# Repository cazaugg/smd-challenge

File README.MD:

# Readme of SMD-Challenge PCB

## Project description

This is a little SMD soldering challenge with Moser Baer branding. Used to teach soldering and teach people about electronics.

Version one used 1206 to 0201 chips and is quite difficult. Version two is simplified and only uses 1206 to 0603 cips.

## Workflow and project organization

- [PCB design and part libraries](pcb/pcb-info.md)
- [Documentation](doc/doc-info.md)
- [Production](prod/prod-info.md)

## Tools

Made with KiCad 7.

***(c)2023 by C. Zaugg***

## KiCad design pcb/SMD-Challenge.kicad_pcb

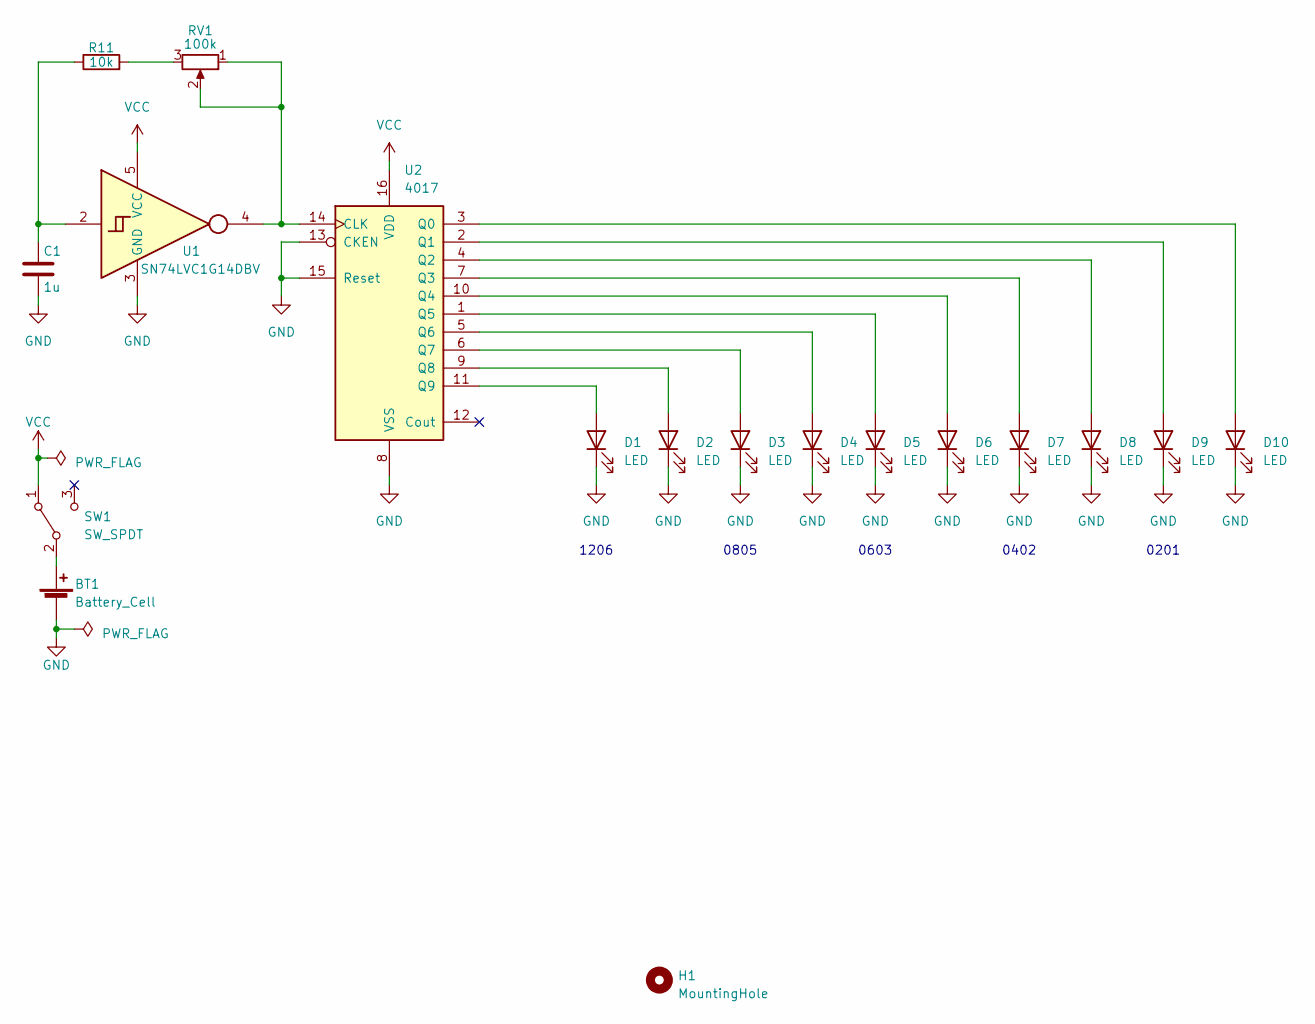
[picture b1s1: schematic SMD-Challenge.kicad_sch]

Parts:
BT1: Battery_Cell; BatteryHolder_Keystone_3002_1x2032
C1: 1u; C_1206_3216Metric
D1, D2: LED; LED_1206_3216Metric
D3, D4: LED; LED_0805_2012Metric
D5, D6: LED; LED_0603_1608Metric
D7, D8: LED; LED_0402_1005Metric
D9, D10: LED; LED_0201_0603Metric
H1: MountingHole; MountingHole_2.2mm_M2
R11: 10k; R_1206_3216Metric
RV1: 100k; Potentiometer_Bourns_TC33X_Vertical
SW1: SW_SPDT; SW_SPDT_PCM12
U1: SN74LVC1G14DBV; SOT-23-5
U2: 4017; SO-16_3.9x9.9mm_P1.27mm

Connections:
GND: BT1.2 (-), C1.2, D1.1 (K), D2.1 (K), D3.1 (K), D4.1 (K), D5.1 (K), D6.1 (K), D7.1 (K), D8.1 (K), D9.1 (K), D10.1 (K), U1.3 (GND), U2.8 (VSS), U2.13 (CKEN), U2.15 (Reset)
unnamed: BT1.1 (+), SW1.2 (B)
unnamed: C1.1, R11.1, U1.2
unnamed: D1.2 (A), U2.11 (Q9)
unnamed: D2.2 (A), U2.9 (Q8)
unnamed: D3.2 (A), U2.6 (Q7)
unnamed: D4.2 (A), U2.5 (Q6)
unnamed: D5.2 (A), U2.1 (Q5)
unnamed: D6.2 (A), U2.10 (Q4)
unnamed: D7.2 (A), U2.7 (Q3)
unnamed: D8.2 (A), U2.4 (Q2)
unnamed: D9.2 (A), U2.2 (Q1)
unnamed: D10.2 (A), U2.3 (Q0)
unnamed: R11.2, RV1.3
unnamed: RV1.1, RV1.2, U1.4, U2.14 (CLK)
VCC: SW1.1 (A), U1.5 (VCC), U2.16 (VDD)

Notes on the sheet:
0201
1206
0805
0402
0603

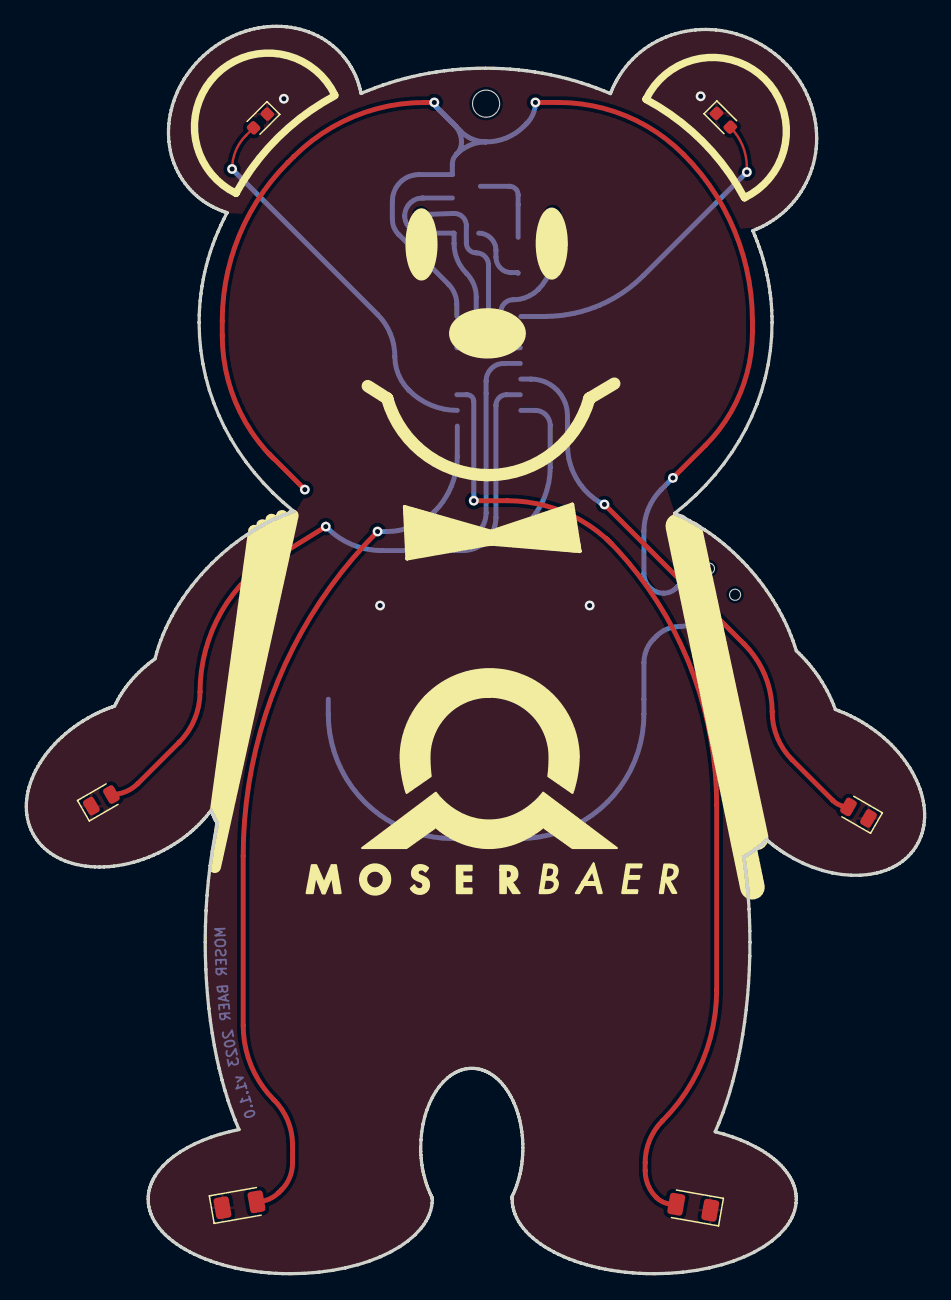
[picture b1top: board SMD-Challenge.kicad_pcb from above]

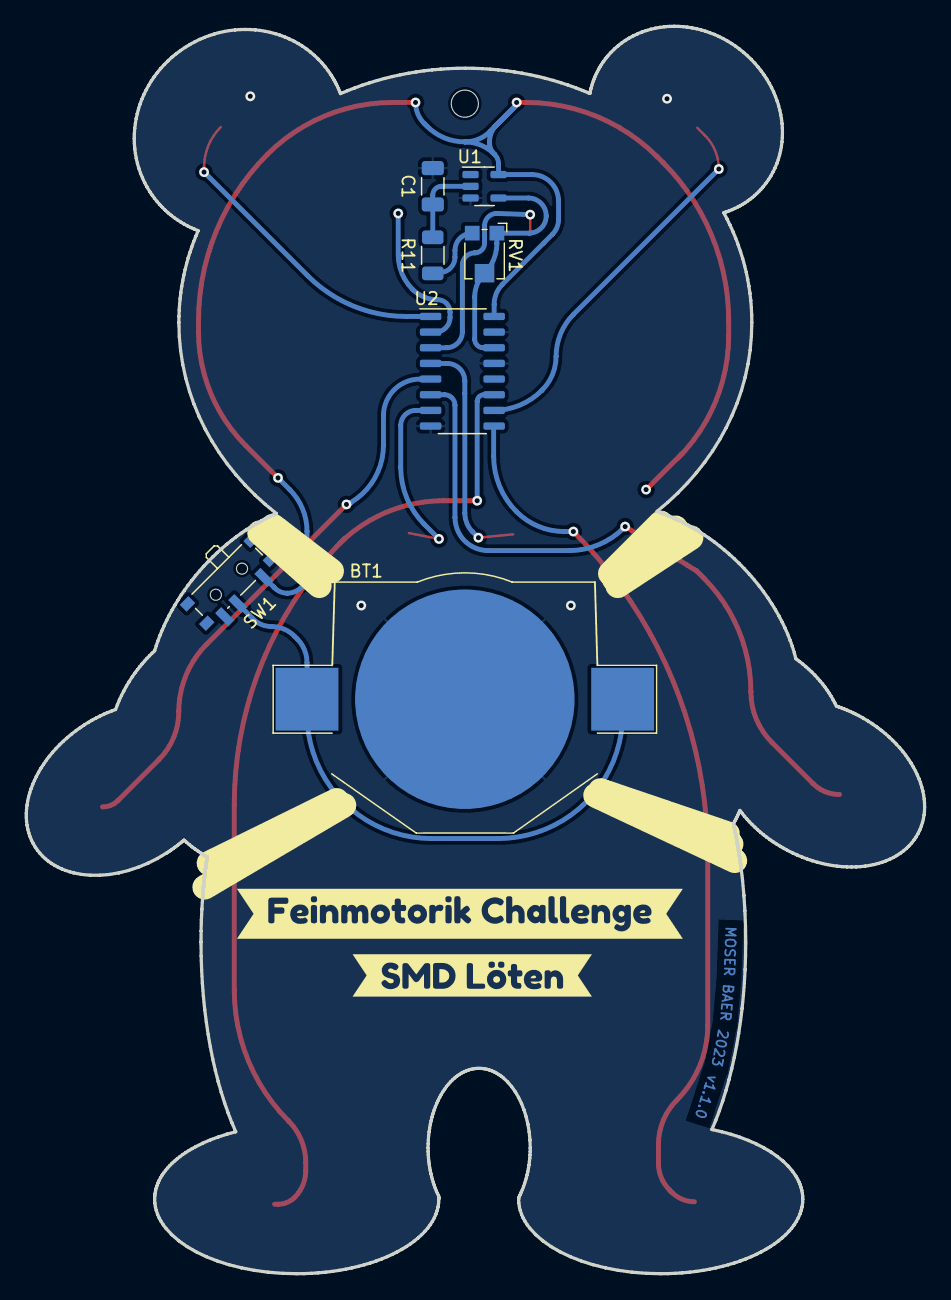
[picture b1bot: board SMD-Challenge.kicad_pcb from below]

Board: 2 copper layers, 72.9 x 101.2 mm, 20 parts (9 on the bottom side), 16 nets.

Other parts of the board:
kibuzzard-63D590DE: G***; kibuzzard-63D590DE
kibuzzard-63D590F7: G***; kibuzzard-63D590F7

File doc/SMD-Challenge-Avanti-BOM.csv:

"#","Reference","Qty","Value","Footprint","DNP"
"1","BT1","1","Battery_Cell","Battery:BatteryHolder_Keystone_3002_1x2032",""
"2","C1","1","1u","Capacitor_SMD:C_1206_3216Metric",""
"3","D1, D2","2","LED","LED_SMD:LED_0603_1608Metric",""
"4","D3, D6","2","LED","LED_SMD:LED_0805_2012Metric",""
"5","D4, D5","2","LED","LED_SMD:LED_1206_3216Metric",""
"6","H1","1","MountingHole","MountingHole:MountingHole_2.5mm",""
"7","R11","1","10k","Resistor_SMD:R_1206_3216Metric",""
"8","RV1","1","100k","Potentiometer_SMD:Potentiometer_Bourns_TC33X_Vertical",""
"9","SW1","1","SW_SPDT","Button_Switch_SMD:SW_SPDT_PCM12",""
"10","U1","1","SN74LVC1G14DBV","Package_TO_SOT_SMD:SOT-23-5",""
"11","U2","1","74HC4017","Package_SO:SO-16_3.9x9.9mm_P1.27mm",""

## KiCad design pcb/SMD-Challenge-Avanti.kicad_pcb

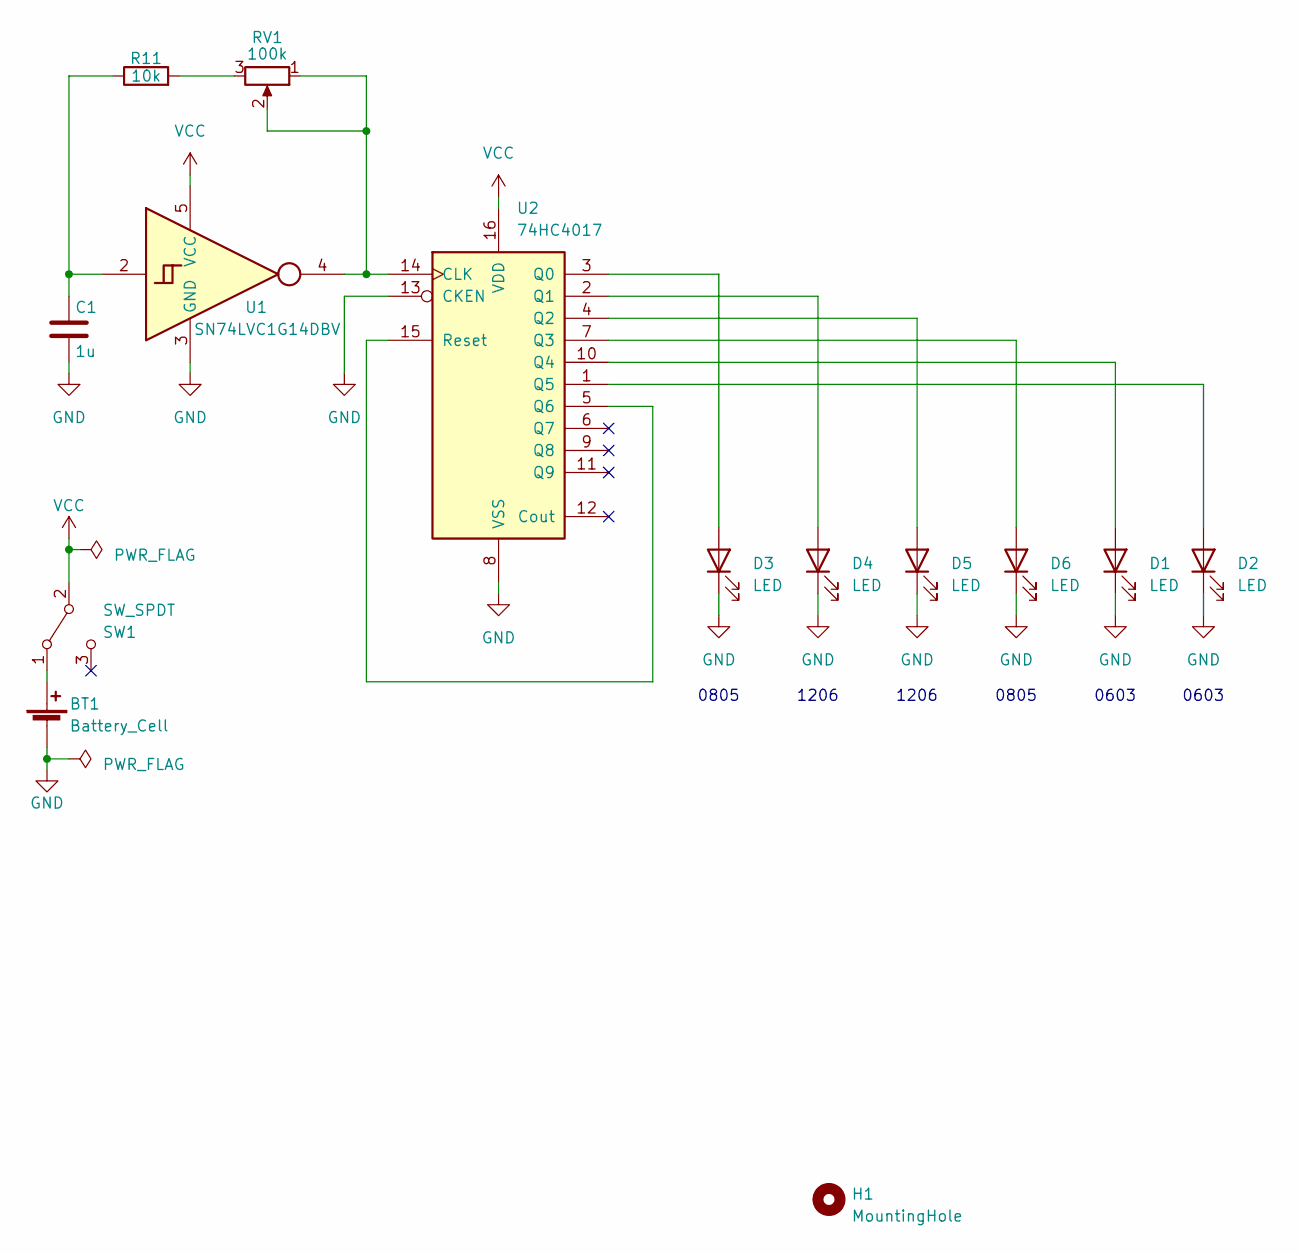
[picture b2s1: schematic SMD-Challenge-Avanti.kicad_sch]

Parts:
BT1: Battery_Cell; BatteryHolder_Keystone_3002_1x2032
C1: 1u; C_1206_3216Metric
D1, D2: LED; LED_0603_1608Metric
D3, D6: LED; LED_0805_2012Metric
D4, D5: LED; LED_1206_3216Metric
H1: MountingHole; MountingHole_2.5mm
R11: 10k; R_1206_3216Metric
RV1: 100k; Potentiometer_Bourns_TC33X_Vertical
SW1: SW_SPDT; SW_SPDT_PCM12
U1: SN74LVC1G14DBV; SOT-23-5
U2: 74HC4017; SO-16_3.9x9.9mm_P1.27mm

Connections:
GND: BT1.2 (-), C1.2, D1.1 (K), D2.1 (K), D3.1 (K), D4.1 (K), D5.1 (K), D6.1 (K), U1.3 (GND), U2.8 (VSS), U2.13 (CKEN)
unnamed: BT1.1 (+), SW1.1 (A)
unnamed: C1.1, R11.1, U1.2
unnamed: D1.2 (A), U2.10 (Q4)
unnamed: D2.2 (A), U2.1 (Q5)
unnamed: D3.2 (A), U2.3 (Q0)
unnamed: D4.2 (A), U2.2 (Q1)
unnamed: D5.2 (A), U2.4 (Q2)
unnamed: D6.2 (A), U2.7 (Q3)
unnamed: R11.2, RV1.3
unnamed: RV1.1, RV1.2, U1.4, U2.14 (CLK)
unnamed: U2.5 (Q6), U2.15 (Reset)
VCC: SW1.2 (B), U1.5 (VCC), U2.16 (VDD)

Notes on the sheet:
1206
0805
0603

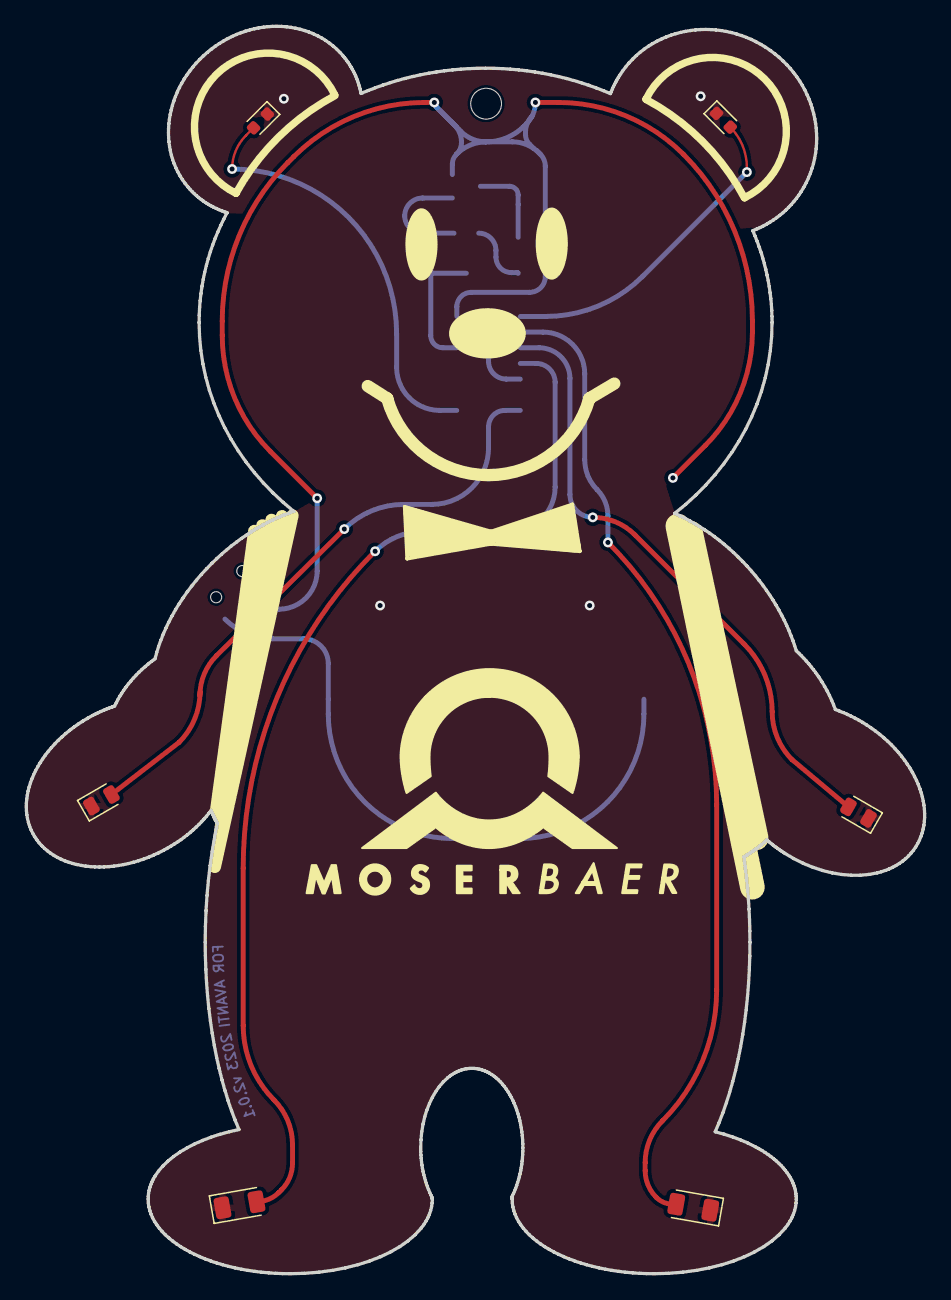
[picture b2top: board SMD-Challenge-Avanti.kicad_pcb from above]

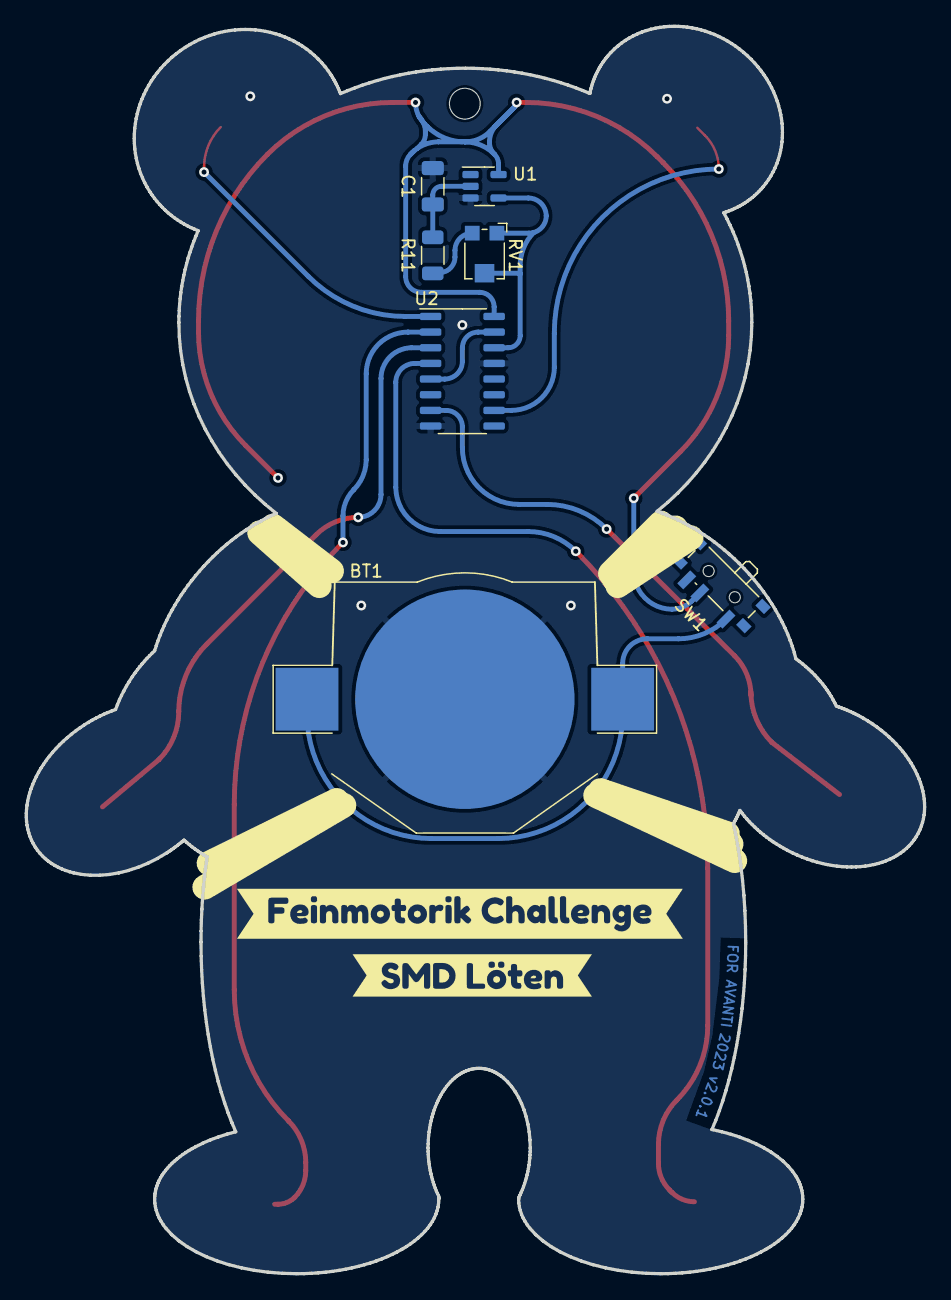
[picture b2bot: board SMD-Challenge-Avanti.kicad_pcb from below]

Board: 2 copper layers, 72.9 x 101.2 mm, 16 parts (9 on the bottom side), 13 nets.

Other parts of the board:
kibuzzard-63D590DE: G***; kibuzzard-63D590DE
kibuzzard-63D590F7: G***; kibuzzard-63D590F7

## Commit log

2022-11-03 Setup repo.
2023-01-30 Add first draft
2023-01-30 Remove verison.txt
2023-02-16 Update to KiCad7
2023-02-16 Updated design
2023-02-21 Add Avanti specific version
2023-02-21 Update Silkscreen
2023-02-21 Update docs
2023-02-27 Fix blink order
2023-02-27 Fix text
2023-02-27 Prepare Release
2023-04-03 Fixed version 1
